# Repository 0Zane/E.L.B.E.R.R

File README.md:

<div align="center">

  <h1>E.L.B.E.R.R.</h1>

  <p>
    A fanmade animatronic robot powered by local AI, embedded control systems,
    and custom hardware.
  </p>

  <p>

  </p>
</div>

---

## Overview

**E.L.B.E.R.R.** is a fanmade animatronic project inspired by the robot featured
in the animations from [LIGHTS ARE OFF](https://www.youtube.com/@LIGHTSAREOFF).

The goal of this project is to recreate the character as a physical animatronic
robot using a custom local AI system, embedded motor control, sensors, and
purpose-built hardware. E.L.B.E.R.R. is designed as a self-contained robot that
can process information locally, control its own actuators, and respond through
real-time embedded systems.

> This is an unofficial fan project. It is not affiliated with, endorsed by, or
> produced by LIGHTS ARE OFF.

<div align="center">
  
  <br />
  <sub>Reference image of the robot from the original animation.</sub>
</div>

---

## Built Robot Gallery

A few photos from the assembled robot, scaled for cleaner viewing in the repository.

<div align="center">
  <table>
    <tr>
      <td align="center"></td>
      <td align="center"></td>
    </tr>
    <tr>
      <td align="center"></td>
      <td align="center"></td>
    </tr>
  </table>
</div>

---

# Architecture

## Core Concept

E.L.B.E.R.R. is built around a three-processor architecture:

* A **Raspberry Pi 5** acts as the primary computer, running the local AI system, behavior engine, perception, and overall robot coordination.
* An **ESP32-S3** serves as the communication and sensing processor, handling environmental sensors, wireless connectivity, and RF communication.
* An **STM32** microcontroller is dedicated to real-time servo and actuator control, ensuring smooth, deterministic motion and reliable animatronic performance.

This separation allows each processor to focus on a specific task while keeping motion control isolated from higher-level software.

The Raspberry Pi 5, ESP32-S3, and STM32 communicate with one another over UART.

```mermaid
flowchart LR
  Camera[Camera] --> Pi[Raspberry Pi 5]
  Mic[Microphone] --> Pi
  Other[Embedded Sensors] --> ESP

  Pi <-->|UART| ESP[ESP32-S3]

  Pi --> AI[Local AI System]
  AI --> Behavior[Behavior Engine]

  Pi <-->|UART| STM[STM32]
  STM --> Servos[Servos]
  STM --> Actuators[Animatronic Actuators]
```

---

## Hardware Architecture

| Subsystem              | Component                                        | Purpose                                                                                     |
| ---------------------- | ------------------------------------------------ | ------------------------------------------------------------------------------------------- |
| Main computer          | Raspberry Pi 5                                   | Local AI, behavior logic, planning, vision processing, networking, and system orchestration |
| Sensor & RF controller | ESP32-S3                                         | Environmental sensors, wireless communication, RF capabilities, and data collection         |
| Motion controller      | STM32                                            | Real-time servo control, actuator control, deterministic timing, and motion safety          |
| Mechanical system      | Animatronic frame                                | Physical movement, expression, and character presence                                       |
| Sensors                | Cameras, microphones, IMUs, and embedded sensors | Environmental input and interaction data                                                    |
| PCB design             | KiCad                                            | Custom circuit design, wiring organization, and hardware integration                        |
| Firmware               | C++                                              | Embedded software for STM32 and ESP32-S3                                                    |

---

## Raspberry Pi 5

The Raspberry Pi 5 is the central computer of E.L.B.E.R.R.

Its responsibilities include:

* Running the local AI system
* Managing high-level robot behavior
* Processing camera, microphone, and perception data
* Coordinating communication between all processors
* Handling networking, logging, and debugging
* Making behavioral decisions before sending motion commands to the STM32

The Pi is responsible for what the robot **thinks**.

---

## ESP32-S3

The ESP32-S3 is dedicated to sensing and wireless communication.

Its responsibilities include:

* Reading environmental sensors
* Monitoring digital and analog inputs
* Handling RF and wireless communication
* Forwarding sensor information to the Raspberry Pi 5
* Providing low-power peripheral management

The ESP32-S3 is responsible for what the robot **perceives** and how it communicates with external devices.

---

## STM32

The STM32 is dedicated to real-time motion control.

Its responsibilities include:

* Driving servos and animatronic actuators
* Generating precise PWM outputs
* Executing smooth motion profiles
* Enforcing movement limits
* Monitoring actuator timing
* Executing commands received from the Raspberry Pi 5

The STM32 is responsible for how the robot **moves**.

---

## Hardware Schematics

The design files in the repository include the core hardware schematics and module layouts for the robot control system.

<div align="center">
  <table>
    <tr>
      <td align="center"><h3>ESP modules</h3></td>
      <td align="center"><h3>ESP32-S3 board</h3></td>
      <td align="center"><h3>Eye module</h3></td>
    </tr>
  </table>
</div>

---

## Project Structure

```text
E.L.B.E.R.R/
|-- 3dmodels/
|-- esp32-firmware/
|   |-- include/
|   |-- lib/
|   |-- src/
|   |-- test/
|   `-- platformio.ini
|-- hardware/
|   |-- README.md
|   |-- esp/
|   |   |-- esp.kicad_pro
|   |   |-- esp.kicad_sch
|   |   |-- esp.kicad_pcb
|   |   |-- bom.csv
|   |   |-- production/
|   |   `-- esp-backups/
|   |-- eyes/
|   |   |-- eyes.kicad_pro
|   |   |-- eyes.kicad_sch
|   |   |-- eyes.kicad_pcb
|   |   |-- bom.csv
|   |   |-- production/
|   |   `-- eyes-backups/
|   |-- stm/
|   |   |-- stm.kicad_pro
|   |   |-- stm.kicad_sch
|   |   |-- stm.kicad_pcb
|   |   |-- stm-backups/
|   |   `-- ...
|   |-- esp.svg
|   |-- eyes.svg
|   `-- modules.svg
|-- pictures/
|   |-- elberr1.webp
|   |-- elberr2.webp
|   |-- elberr3.webp
|   `-- elberr4.webp
|-- software/
|   |-- README.md
|   |-- Modelfile
|   |-- boot.py
|   |-- llm.py
|   |-- main.py
|   |-- requirements.txt
|   |-- stt.py
|   |-- tts.py
|   `-- memory/
|-- stm32-firmware/
|   |-- Core/
|   |-- Drivers/
|   |-- EWARM/
|   |-- stm32-firmware.ioc
|   `-- ...
|-- index.html
|-- elberr.jpg
|-- elberr.png
|-- README.md
|-- LICENSE
`-- .gitignore (if present)
```

---

## Technologies

| Area              | Technology                  |
| ----------------- | --------------------------- |
| Main compute      | Raspberry Pi 5              |
| Sensor processor  | ESP32-S3                    |
| Motion controller | STM32                       |
| Firmware          | C++                         |
| PCB design        | KiCad                       |
| 3D modeling       | Fusion 360                  |
| AI                | Local custom AI system      |
| Architecture      | Distributed embedded system |

---

## Inspiration

This project is inspired by the robot created in the animations from
[LIGHTS ARE OFF](https://www.youtube.com/@LIGHTSAREOFF).

E.L.B.E.R.R. is a fanmade physical interpretation of that concept, built as a
personal robotics, AI, and embedded systems project.

---

## Credits

Special thanks to the people who helped along the way:

- ESP PCB review: [Estylos](https://github.com/Estylos)
- Help with STM32 project setup: [Pupariaa](https://github.com/Pupariaa)

---

## License

This project is licensed under the **MIT License**.

See the [LICENSE](./LICENSE) file for details.

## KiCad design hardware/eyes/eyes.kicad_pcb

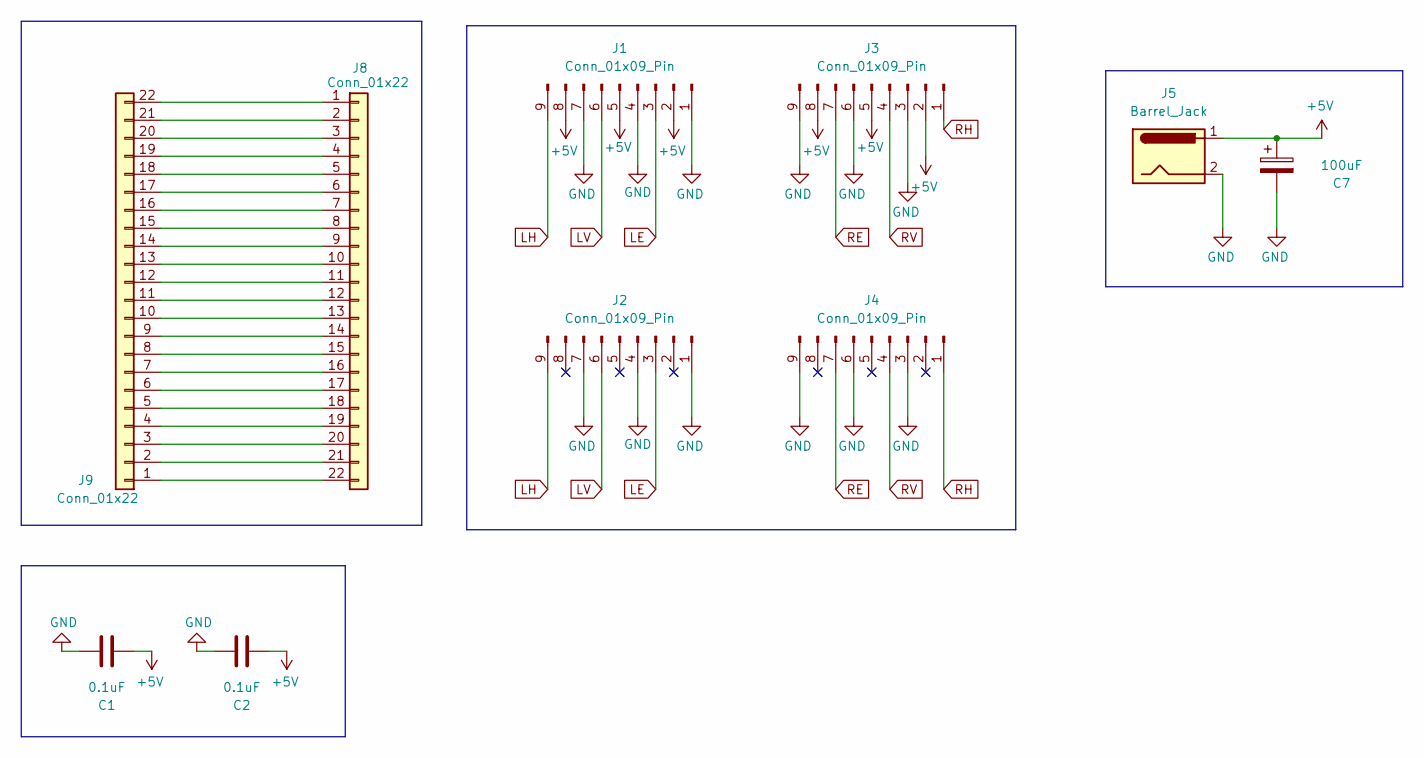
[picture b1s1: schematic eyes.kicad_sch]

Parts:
C1, C2: 0.1uF; C_0805_2012Metric
C7: 100uF; CP_Radial_D8.0mm_P3.50mm
J1, J2, J3, J4: Conn_01x09_Pin; PinHeader_1x09_P2.54mm_Vertical
J5: Barrel_Jack; BarrelJack_Horizontal
J8, J9: Conn_01x22; Amphenol_F32Q-1A7x1-11022_1x22-1MP_P0.5mm_Horizontal

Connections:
+5V: C1.1, C2.1, C7.1, J1.2, J1.5, J1.8, J3.2, J3.5, J3.8, J5.1
GND: C1.2, C2.2, C7.2, J1.1, J1.4, J1.7, J2.1, J2.4, J2.7, J3.3, J3.6, J3.9, J4.3, J4.6, J4.9, J5.2
LE: J1.3, J2.3
LH: J1.9, J2.9
LV: J1.6, J2.6
unnamed: J8.1, J9.22
unnamed: J8.2, J9.21
unnamed: J8.3, J9.20
unnamed: J8.4, J9.19
unnamed: J8.5, J9.18
unnamed: J8.6, J9.17
unnamed: J8.7, J9.16
unnamed: J8.8, J9.15
unnamed: J8.9, J9.14
unnamed: J8.10, J9.13
unnamed: J8.11, J9.12
unnamed: J8.12, J9.11
unnamed: J8.13, J9.10
unnamed: J8.14, J9.9
unnamed: J8.15, J9.8
unnamed: J8.16, J9.7
unnamed: J8.17, J9.6
unnamed: J8.18, J9.5
unnamed: J8.19, J9.4
unnamed: J8.20, J9.3
unnamed: J8.21, J9.2
unnamed: J8.22, J9.1
RE: J3.7, J4.7
RH: J3.1, J4.1
RV: J3.4, J4.4

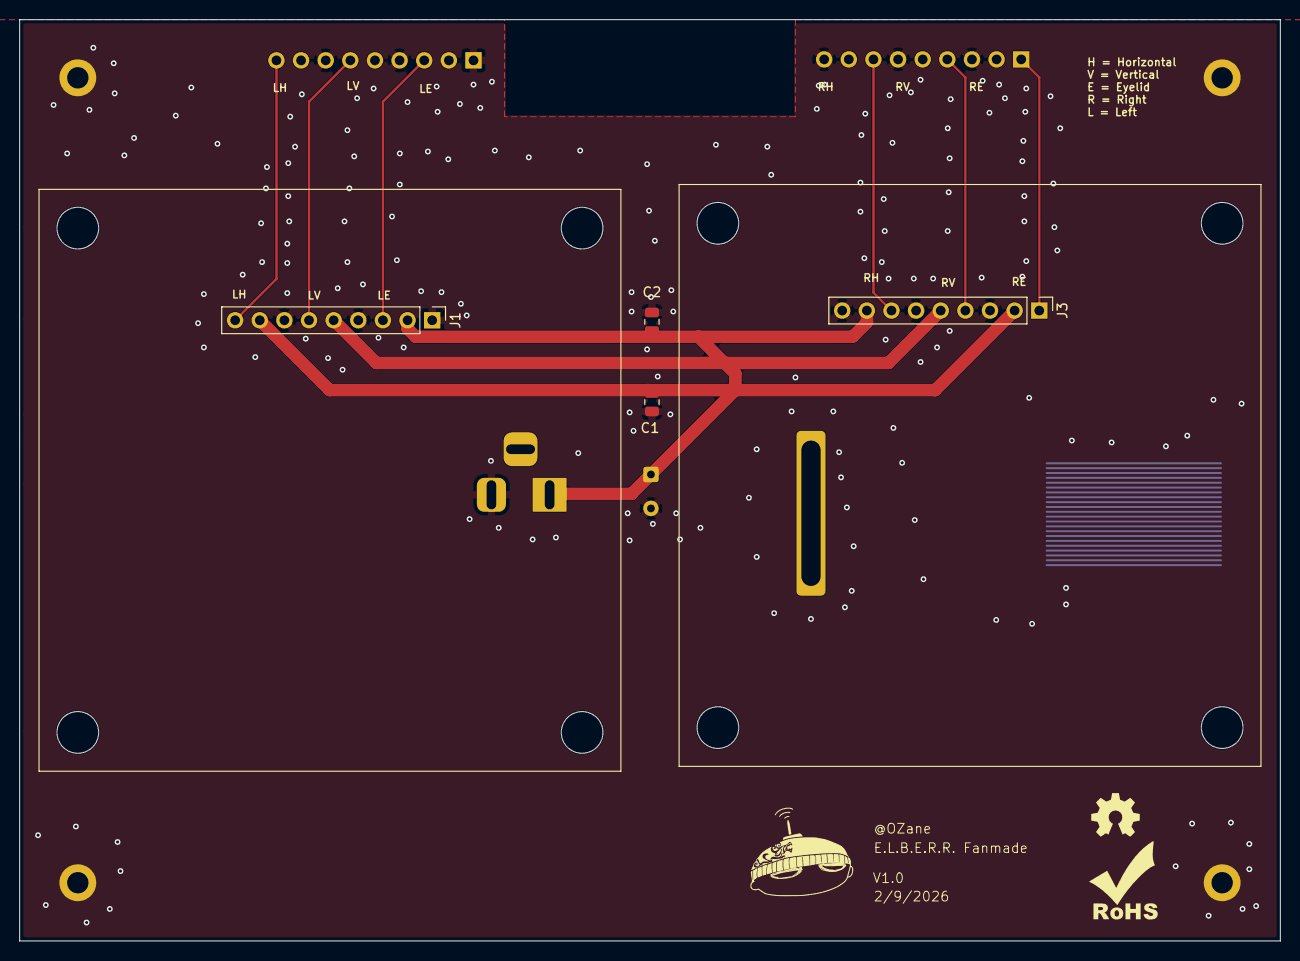
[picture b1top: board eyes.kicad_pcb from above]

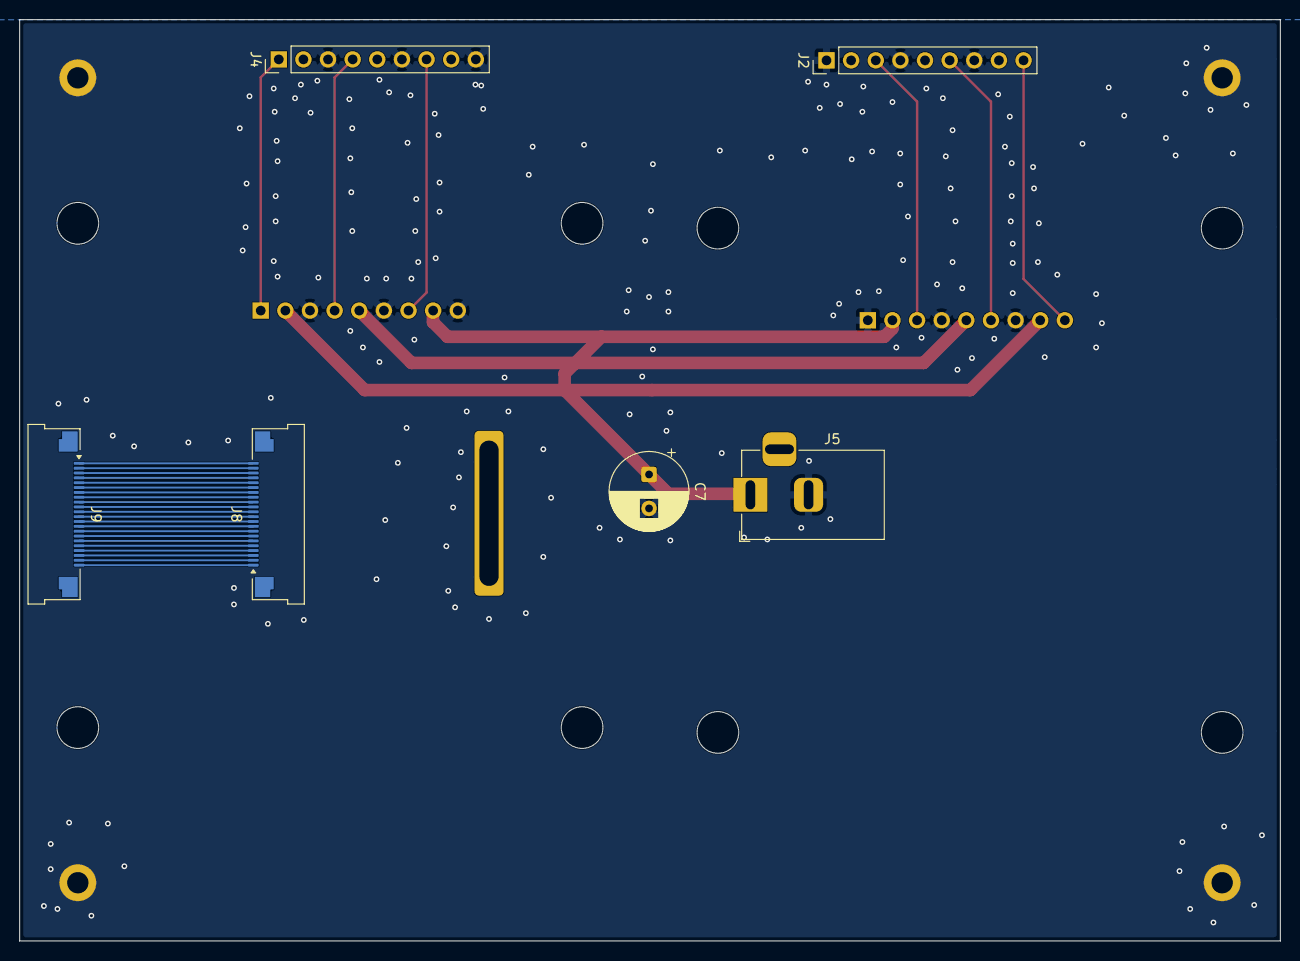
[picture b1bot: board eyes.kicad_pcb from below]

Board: 2 copper layers, 130.0 x 95.0 mm, 10 parts (6 on the bottom side), 30 nets.

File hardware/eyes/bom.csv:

"Reference","Qty","Value","DNP","Exclude from BOM","Exclude from Board","Footprint","Datasheet"
"C1,C2","2","0.1uF","","","","Capacitor_SMD:C_0805_2012Metric",""
"C7","1","100uF","","","","Capacitor_THT:CP_Radial_D8.0mm_P3.50mm",""
"J1,J2,J3,J4","4","Conn_01x09_Pin","","","","Connector_PinHeader_2.54mm:PinHeader_1x09_P2.54mm_Vertical",""
"J5","1","Barrel_Jack","","","","Connector_BarrelJack:BarrelJack_Horizontal",""
"J8,J9","2","Conn_01x22","","","","Connector_FFC-FPC:Amphenol_F32Q-1A7x1-11022_1x22-1MP_P0.5mm_Horizontal",""

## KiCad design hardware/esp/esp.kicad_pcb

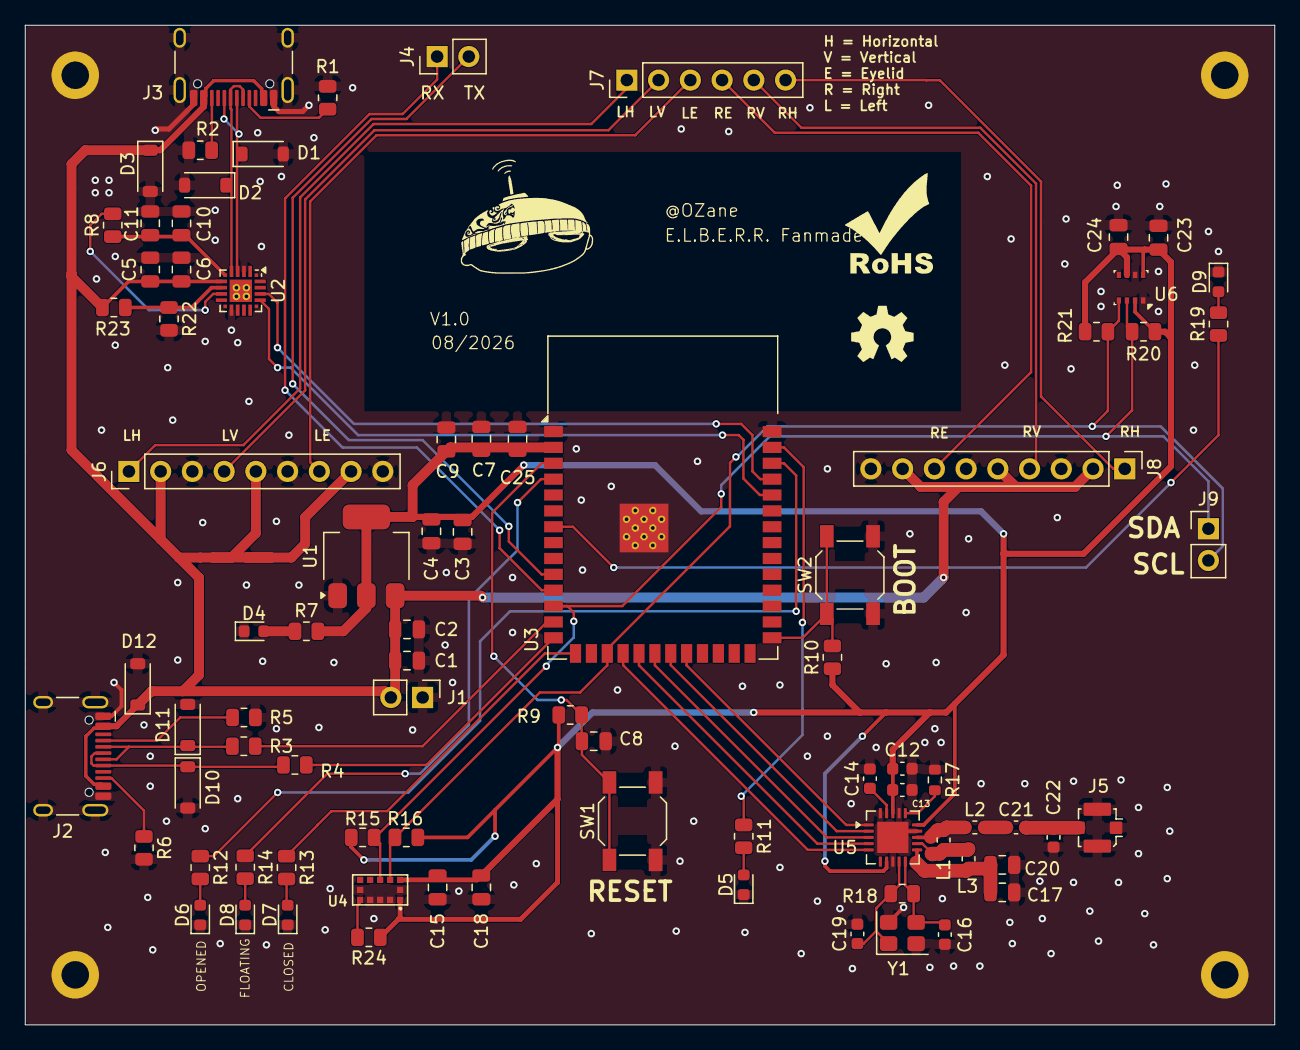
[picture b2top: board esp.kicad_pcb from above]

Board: 2 copper layers, 100.0 x 80.0 mm, 82 parts (0 on the bottom side), 56 nets.

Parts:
C1, C3, C7, C9: 10uF; C_0805_2012Metric
C2, C4, C6, C10, C15, C23, C24, C25: 0.1uF; C_0805_2012Metric
C5, C11, C18: 4.7uF; C_0805_2012Metric
C8: 0.1µF; C_0805_2012Metric
C12: 10nF; C_0603_1608Metric
C13: 1nF; C_0603_1608Metric
C14: 33nF; C_0603_1608Metric
C16, C19: 22pF; C_0603_1608Metric
C17: 2.2nF; C_0805_2012Metric
C20: 4.7pF; C_0805_2012Metric
C21: 1.5pF; C_0603_1608Metric
C22: 1pF; C_0603_1608Metric
D1, D2, D3, D10, D11, D12: D_TVS; D_SOD-123
D4, D5, D6, D7, D8, D9: LED; LED_0603_1608Metric
J1, J4, J9: Conn_01x02; PinHeader_1x02_P2.54mm_Vertical
J2, J3: USB_C_Receptacle_USB2.0_16P; USB_C_Receptacle_HCTL_HC-TYPE-C-16P-01A
J5: Conn_Coaxial; U.FL_Molex_MCRF_73412-0110_Vertical
J6, J8: Conn_01x09_Pin; PinHeader_1x09_P2.54mm_Vertical
J7: Conn_01x06_Pin; PinHeader_1x06_P2.54mm_Vertical
L1: 8.2nH; L_0603_1608Metric
L2: 3.9nH; L_0603_1608Metric
L3: 2.7nH; L_0603_1608Metric
R1, R2, R5, R6: 5.1k; R_0805_2012Metric
R3, R4: 22R; R_0805_2012Metric
R7, R8, R11, R12, R13, R14, R19: 1k; R_0805_2012Metric
R9, R24: 10k; R_0805_2012Metric
R10: 10K; R_0805_2012Metric
R15, R16, R20, R21: 4.7k; R_0805_2012Metric
R17: 22K; R_0603_1608Metric
R18: 1M; R_0805_2012Metric
R22: 47.5k; R_0805_2012Metric
R23: 22.1k; R_0805_2012Metric
SW1: RESET; SW_SPST_SKQG_WithStem
SW2: BOOT; SW_SPST_SKQG_WithStem
U1: AMS1117-3.3; SOT-223-3_TabPin2
U2: CP2102N-Axx-xQFN20; SiliconLabs_QFN-20-1EP_3x3mm_P0.5mm_EP1.8x1.8mm
U3: ESP32-S3-WROOM-1
U4: VL53L0X; SENSOR_VL53L0X
U5: NRF24L01; QFN-20-1EP_4x4mm_P0.5mm_EP2.5x2.5mm
U6: BME280; Bosch_LGA-8_2.5x2.5mm_P0.65mm_ClockwisePinNumbering
Y1: 16MHz; Crystal_SMD_3225-4Pin_3.2x2.5mm

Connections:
+3V3: C3.1, C4.1, C7.2, C9.2, C12.2, C13.2, C15.1, C18.1, C23.2, C24.2, C25.2, R7.2, R9.2, R10.1, R15.1, R16.1, R20.2, R21.2, R24.1, U1.2 (VO), U3.2 (3V3), U4.1 (AVDDVCSEL), U4.11 (AVDD), U5.7 (VDD), U5.15 (VDD), U5.18 (VDD), U6.2 (CSB), U6.6 (VDDIO), U6.8 (VDD)
+5V: C1.1, C2.1, C5.1, C6.1, D3.1 (A1), D12.1 (A1), J1.2, J2.A4 (VBUS), J2.A9 (VBUS), J2.B4 (VBUS), J2.B9 (VBUS), J3.A4 (VBUS), J3.A9 (VBUS), J3.B4 (VBUS), J3.B9 (VBUS), J6.2, J6.5, J6.8, J8.2, J8.5, J8.8, R23.1, U1.3 (VI), U2.7 (VREGIN)
/VDD: C10.1, C11.1, R8.1, U2.6 (VDD)
BOOT: R10.2, SW2.1, U3.27 (IO0)
C.SKULL: R13.1, U3.15 (IO3)
D+: R4.2, U3.14 (USB_D+)
D-: R3.2, U3.13 (USB_D-)
EN: C8.2, R9.1, SW1.1, U3.3 (EN)
GND: C1.2, C2.2, C3.2, C4.2, C5.2, C6.2, C7.1, C8.1, C9.1, C10.2, C11.2, C12.1, C13.1, C14.2, C15.2, C16.1, C17.2, C18.2, C19.2, C20.2, C22.1, C23.1, C24.1, C25.1, D1.2 (A2), D2.2 (A2), D3.2 (A2), D4.1 (K), D5.1 (K), D6.1 (K), D7.1 (K), D8.1 (K), D9.1 (K), D10.2 (A2), D11.2 (A2), D12.2 (A2), J1.1, J2.A1 (GND), J2.A12 (GND), J2.B1 (GND), J2.B12 (GND), J2.SH (SHIELD), J3.A1 (GND), J3.A12 (GND), J3.B1 (GND), J3.B12 (GND), J3.SH (SHIELD), J5.2 (Ext), J6.3, J6.6, J6.9, J8.3, J8.6, J8.9, R1.2, R2.2, R5.2, R6.2, R17.1, R22.2, SW1.2, SW2.2, U1.1 (GND), U2.3 (GND), U2.12 (GND), U2.21 (GND), U3.1 (GND), U3.40 (GND), U3.41 (GND), U4.2 (AVSSVCSEL), U4.3 (GND), U4.4 (GND), U4.6 (GND), U4.12 (GND), U5.8 (VSS), U5.14 (VSS), U5.17 (VSS), U5.20 (VSS), U5.21 (VSS), U6.1 (GND), U6.7 (GND), Y1.2 (G), Y1.4 (G)
LE: J6.7, J7.3
LH: J6.1, J7.1
LV: J6.4, J7.2
MISO: U3.18 (IO10), U5.5 (MISO)
MOSI: U3.19 (IO11), U5.4 (MOSI)
NF.SKULL: R14.1, U3.4 (IO4)
NRFLED: R11.1, U3.39 (IO1)
NRF_CE: U3.22 (IO14), U5.1 (CE)
NRF_CSN: U3.21 (IO13), U5.2 (CSN)
unnamed: C21.1, L2.2
unnamed: D1.1 (A1), J3.A6 (D+), J3.B6 (D+), U2.4 (D+)
unnamed: D2.1 (A1), J3.A7 (D-), J3.B7 (D-), U2.5 (D-)
unnamed: D4.2 (A), R7.1
unnamed: D5.2 (A), R11.2
unnamed: D6.2 (A), R12.2
unnamed: D7.2 (A), R13.2
unnamed: D8.2 (A), R14.2
unnamed: D9.2 (A), R19.2
unnamed: D10.1 (A1), J2.A6 (D+), J2.B6 (D+), R4.1
unnamed: D11.1 (A1), J2.A7 (D-), J2.B7 (D-), R3.1
unnamed: J2.A5 (CC1), R5.1
unnamed: J2.B5 (CC2), R6.1
unnamed: J3.A5 (CC1), R1.1
unnamed: J3.B5 (CC2), R2.1
unnamed: C21.2, C22.2, J5.1 (In)
unnamed: R22.1, R23.2, U2.8 (VBUS)
unnamed: R8.2, U2.9 (~RST)
unnamed: R24.2, U4.5 (~XSHUT)
unnamed: L1.2, L3.1, U5.12 (ANT1)
unnamed: L1.1, L2.1, U5.13 (ANT2)
unnamed: C14.1, U5.19 (DVDD)
unnamed: R17.2, U5.16 (IREF)
unnamed: C17.1, C20.1, L3.2, U5.11 (VDD_PA)
unnamed: C16.2, R18.1, U5.10 (XC1), Y1.3
unnamed: C19.1, R18.2, U5.9 (XC2), Y1.1
O.SKULL: R12.1, U3.38 (IO2)
RE: J7.4, J8.7
RH: J7.6, J8.1
RV: J7.5, J8.4
RX: U2.18 (TXD), U3.37 (TXD0)
RX2: J4.1, U3.11 (IO18)
SCK: U3.20 (IO12), U5.3 (SCK)
SCL: J9.2, R16.2, R21.1, U3.17 (IO9), U4.10 (SCL), U6.4 (SCK)
SDA: J9.1, R15.2, R20.1, U3.12 (IO8), U4.9 (SDA), U6.3 (SDI)
TEMP_LED: R19.1, U3.7 (IO7)
TX: U2.17 (RXD), U3.36 (RXD0)
TX2: J4.2, U3.10 (IO17)

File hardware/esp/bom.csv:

"Reference","Value","Footprint","Qty","DNP"
"C1,C3,C7,C9","10uF","Capacitor_SMD:C_0805_2012Metric","4",""
"C2,C4,C6,C10,C15,C23,C24,C25","0.1uF","Capacitor_SMD:C_0805_2012Metric","8",""
"C5,C11,C18","4.7uF","Capacitor_SMD:C_0805_2012Metric","3",""
"C8","0.1µF","Capacitor_SMD:C_0805_2012Metric","1",""
"C12","10nF","Capacitor_SMD:C_0603_1608Metric","1",""
"C13","1nF","Capacitor_SMD:C_0603_1608Metric","1",""
"C14","33nF","Capacitor_SMD:C_0603_1608Metric","1",""
"C16,C19","22pF","Capacitor_SMD:C_0603_1608Metric","2",""
"C17","2.2nF","Capacitor_SMD:C_0805_2012Metric","1",""
"C20","4.7pF","Capacitor_SMD:C_0805_2012Metric","1",""
"C21","1.5pF","Capacitor_SMD:C_0603_1608Metric","1",""
"C22","1pF","Capacitor_SMD:C_0603_1608Metric","1",""
"D1,D2,D3,D10,D11,D12","D_TVS","Diode_SMD:D_SOD-123","6",""
"D4,D5,D6,D7,D8,D9","LED","LED_SMD:LED_0603_1608Metric","6",""
"J1,J4,J9","Conn_01x02","Connector_PinHeader_2.54mm:PinHeader_1x02_P2.54mm_Vertical","3",""
"J2,J3","USB_C_Receptacle_USB2.0_16P","Connector_USB:USB_C_Receptacle_HCTL_HC-TYPE-C-16P-01A","2",""
"J5","Conn_Coaxial","Connector_Coaxial:U.FL_Molex_MCRF_73412-0110_Vertical","1",""
"J6,J8","Conn_01x09_Pin","Connector_PinHeader_2.54mm:PinHeader_1x09_P2.54mm_Vertical","2",""
"J7","Conn_01x06_Pin","Connector_PinHeader_2.54mm:PinHeader_1x06_P2.54mm_Vertical","1",""
"L1","8.2nH","Inductor_SMD:L_0603_1608Metric","1",""
"L2","3.9nH","Inductor_SMD:L_0603_1608Metric","1",""
"L3","2.7nH","Inductor_SMD:L_0603_1608Metric","1",""
"R1,R2,R5,R6","5.1k","Resistor_SMD:R_0805_2012Metric","4",""
"R3,R4","22R","Resistor_SMD:R_0805_2012Metric","2",""
"R7,R8,R11,R12,R13,R14,R19","1k","Resistor_SMD:R_0805_2012Metric","7",""
"R9,R24","10k","Resistor_SMD:R_0805_2012Metric","2",""
"R10","10K","Resistor_SMD:R_0805_2012Metric","1",""
"R15,R16,R20,R21","4.7k","Resistor_SMD:R_0805_2012Metric","4",""
"R17","22K","Resistor_SMD:R_0603_1608Metric","1",""
"R18","1M","Resistor_SMD:R_0805_2012Metric","1",""
"R22","47.5k","Resistor_SMD:R_0805_2012Metric","1",""
"R23","22.1k","Resistor_SMD:R_0805_2012Metric","1",""
"SW1","RESET","Button_Switch_SMD:SW_SPST_SKQG_WithStem","1",""
"SW2","BOOT","Button_Switch_SMD:SW_SPST_SKQG_WithStem","1",""
"U1","AMS1117-3.3","Package_TO_SOT_SMD:SOT-223-3_TabPin2","1",""
"U2","CP2102N-Axx-xQFN20","Package_DFN_QFN:SiliconLabs_QFN-20-1EP_3x3mm_P0.5mm_EP1.8x1.8mm","1",""
"U3","ESP32-S3-WROOM-1","RF_Module:ESP32-S3-WROOM-1","1",""
"U4","VL53L0X","VL53L0X:SENSOR_VL53L0X","1",""
"U5","NRF24L01","Package_DFN_QFN:QFN-20-1EP_4x4mm_P0.5mm_EP2.5x2.5mm","1",""
"U6","BME280","Package_LGA:Bosch_LGA-8_2.5x2.5mm_P0.65mm_ClockwisePinNumbering","1",""
"Y1","16MHz","Crystal:Crystal_SMD_3225-4Pin_3.2x2.5mm","1",""

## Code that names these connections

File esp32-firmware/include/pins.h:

//I2C BUS 
#define I2C_SCL 9
#define I2C_SDA 8

//SPI BUS
#define SPI_MOSI 11
#define SPI_MISO 10
#define SPI_SCK 12
#define NRF_CSN 13
#define NRF_CE 14

//UART WITH RASPBERRY PI
#define UART1_RX_PIN 17
#define  UART1_TX_PIN 18

//LED
#define NRFLED 1
#define OSKULLLED 2
#define CSKULLLED 3
#define NFSKULLLED 4
#define TEMPLED 7

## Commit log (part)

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2026-05-31 Updating project structure and documentation
2026-05-31 Adding web page
2026-06-12 Adding webpage
2026-06-12 fixing file paths, moving webpage to root for github pages deployment
2026-06-21 Uploading robot image to get permalink
2026-06-21 Documentation rebase
2026-06-23 Adding pcb files
2026-06-23 Recreating kicad project after path problem
2026-06-26 PCB first commits
2026-06-28 Adding ESP PCB files
2026-06-29 Updating main.cpp after structure redifining
    removing servi tasks
2026-06-30 Relocalizing firmware dedicated to est32 in a dedicated folder, Creating new header files and cleaning old servo motor control code.

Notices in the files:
README.md:
License: MIT
